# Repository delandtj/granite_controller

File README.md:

# granite

The Granite immersion frame electronics: the 48 V power plane, the
plane-core firmware, the controller and the software shared between them.

granite_controller and granite-plane merged on 2026-10-30. granite-plane
was split from granite_controller on 2026-10-29; its commits were replayed
on top of granite_controller's history, so both histories are here.

## Layout

- controller-fd: the controller with the CAN FD plane link (ADR 0006),
  the live design. tools/fd_build.sh builds it from the rev D board in
  attic/controller-rev-d.
- controller-rev-c: the rev C controller board (relays, expanders, 19 V
  input), kept as demoware. Tag rev-c-demo is the last rev C state of
  the whole repo, firmware included.
- power/pp-48-fd: plane tools and libraries for the CAN FD link
  (ADR 0006). power/pp-48-core-fd, power/pp-48-unit-fd: the chained plane
  (ADR 0005), one core board and identical 2-slot unit boards.
- power/pp-48: the I2C-link plane tools (schematic generator, placement
  and routing scripts), pp.kicad_sym, pp48.pretty, pp48.3dshapes; its
  schematic engine is also used by pm-19v-250w-b, and the attic boards
  use its libraries.
- power/pm-19v-250w, power/pm-19v-250w-b: the port module. power/pm-bench-carrier: bench
  carrier for one module. power/tools: module mount geometry.
- site: installer / operator manual (mdBook). Still describes rev C
  (relays, expanders, 19 V input); to be reworked for rev D and the plane.
- firmware: Rust workspace. granite-core (no_std: dispatcher, commands,
  MQTT / HTTP / Modbus surfaces, rules, config), granite-sim (host
  simulator), granite-fw (ESP32-C6 binary, still the rev C hardware
  layer), web UI.
- docs: ADRs 0001-0007, plane requirements, module interface, controller
  specs, handoff. Firmware ADRs in firmware/docs/adr.
- attic: superseded designs, kept for reference, not maintained.
  - attic/power/pp-48-2s: the first 2-slot plane (ADR 0001 / 0002).
  - attic/power/pm-19v-200w: the first port module (obsolete since
    2026-10-27, replaced by pm-19v-250w).
  - attic/power/pp-48-rev1: the single-board plane (ADR 0004, tag
    pp48-rev1); uses the libraries in power/pp-48.
  - attic/controller-rev-d: the I2C-link controller (rev D), superseded
    by controller-fd (2026-11-10); still the input board of
    controller-fd/tools/fd_build.sh.
  - attic/power/pp-48-core, attic/power/pp-48-unit: the I2C-link chained
    plane (ADR 0005), superseded by the -fd boards (2026-11-10); still the
    input boards of power/pp-48-fd/tools/fd_layout.sh and the output of
    power/pp-48/tools/gensch.py.
  - attic/firmware/plane-fw, attic/firmware/plane-core-pins.toml: the
    rev D plane binary (I2C link) and its pin map, frozen 2026-11-10;
    builds against firmware/granite-proto and firmware/plane-logic. The
    FD plane binary is firmware/plane-fd (firmware ADR 0005 decision 9).
  Older docs and the handoff name these at their old paths
  (power/pp-48-2s, power/pm-19v-200w, power/pp-48/pp-48.kicad_*,
  controller, power/pp-48-core, power/pp-48-unit).

## Direction (decided 2026-10-29)

- Plane core firmware on the STM32G070 (embassy), I2C slave to the
  controller, master to the units through the TCA9548A.
- Plane firmware updated from the controller over the link: own A/B
  bootloader (embassy-boot) that keeps the plane's strapped address,
  rollback on a failed self-test. ST's ROM bootloader only as a bench
  recovery path.
- The plane core owns node sequencing (press deadlines, power-cycle,
  retry / latch policy, stagger); the controller does policy, rules and
  the network.
- One controller serves several planes over isolated I2C (ISO1640 +
  EXP_INT, daisy chain, plane addresses 0x30-0x37).
- One TLV protocol crate used by the plane firmware, the controller and
  the simulator.
- Controller rev D: rev C minus the relays, expanders, LED sense and
  19 V input; 12 V from the plane's isolated aux.

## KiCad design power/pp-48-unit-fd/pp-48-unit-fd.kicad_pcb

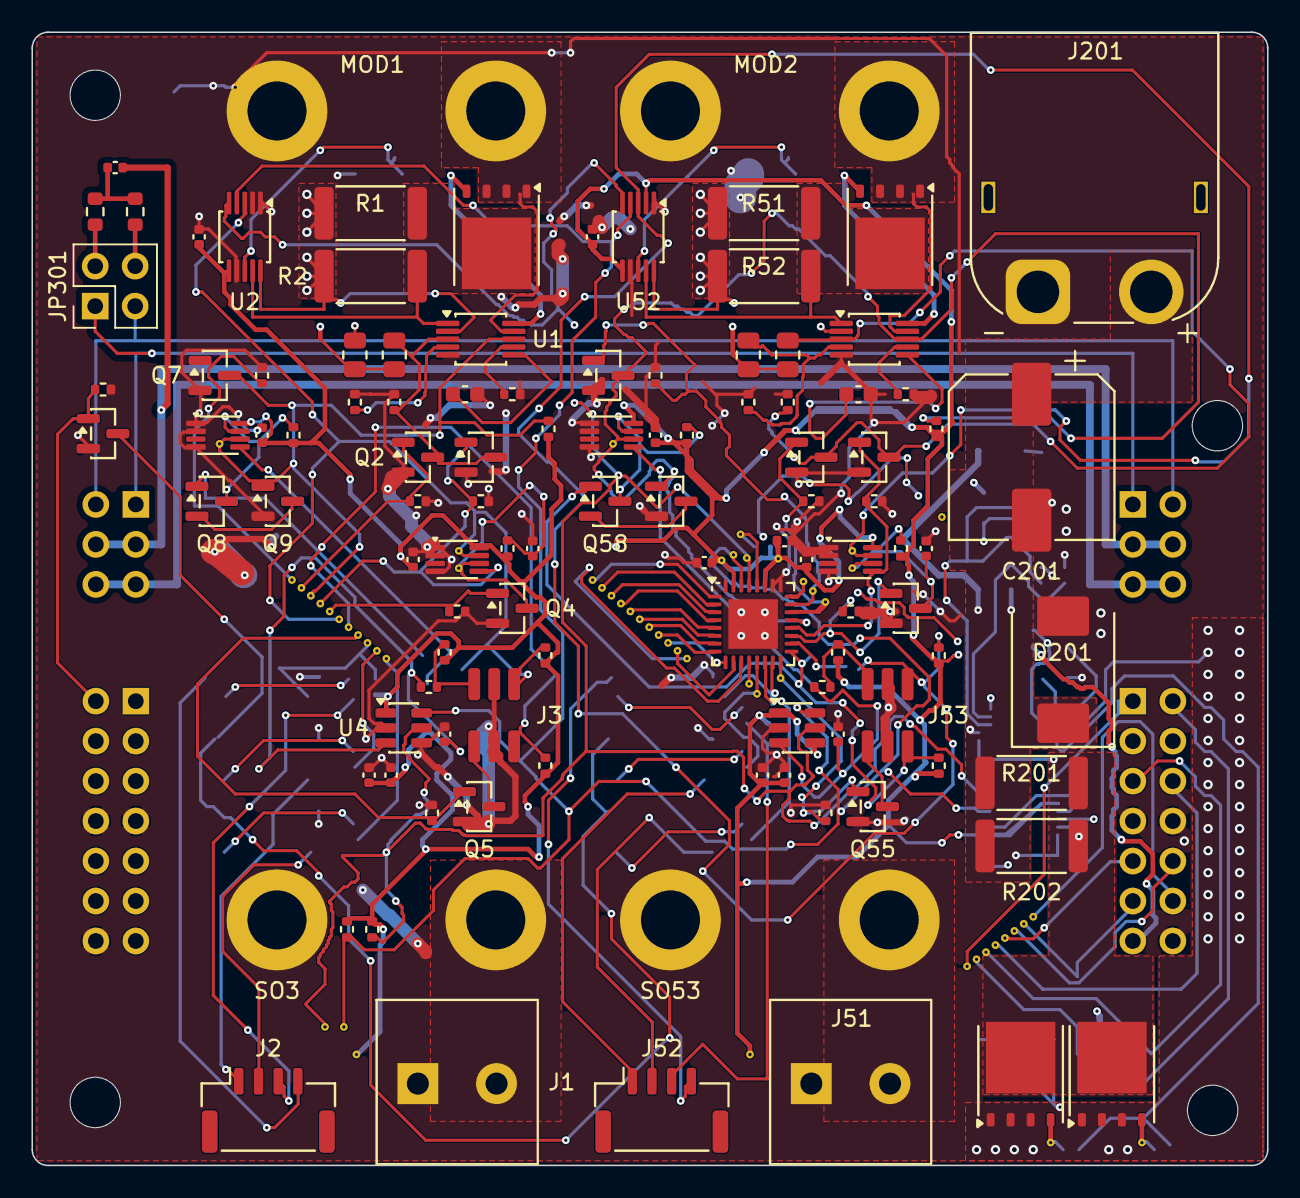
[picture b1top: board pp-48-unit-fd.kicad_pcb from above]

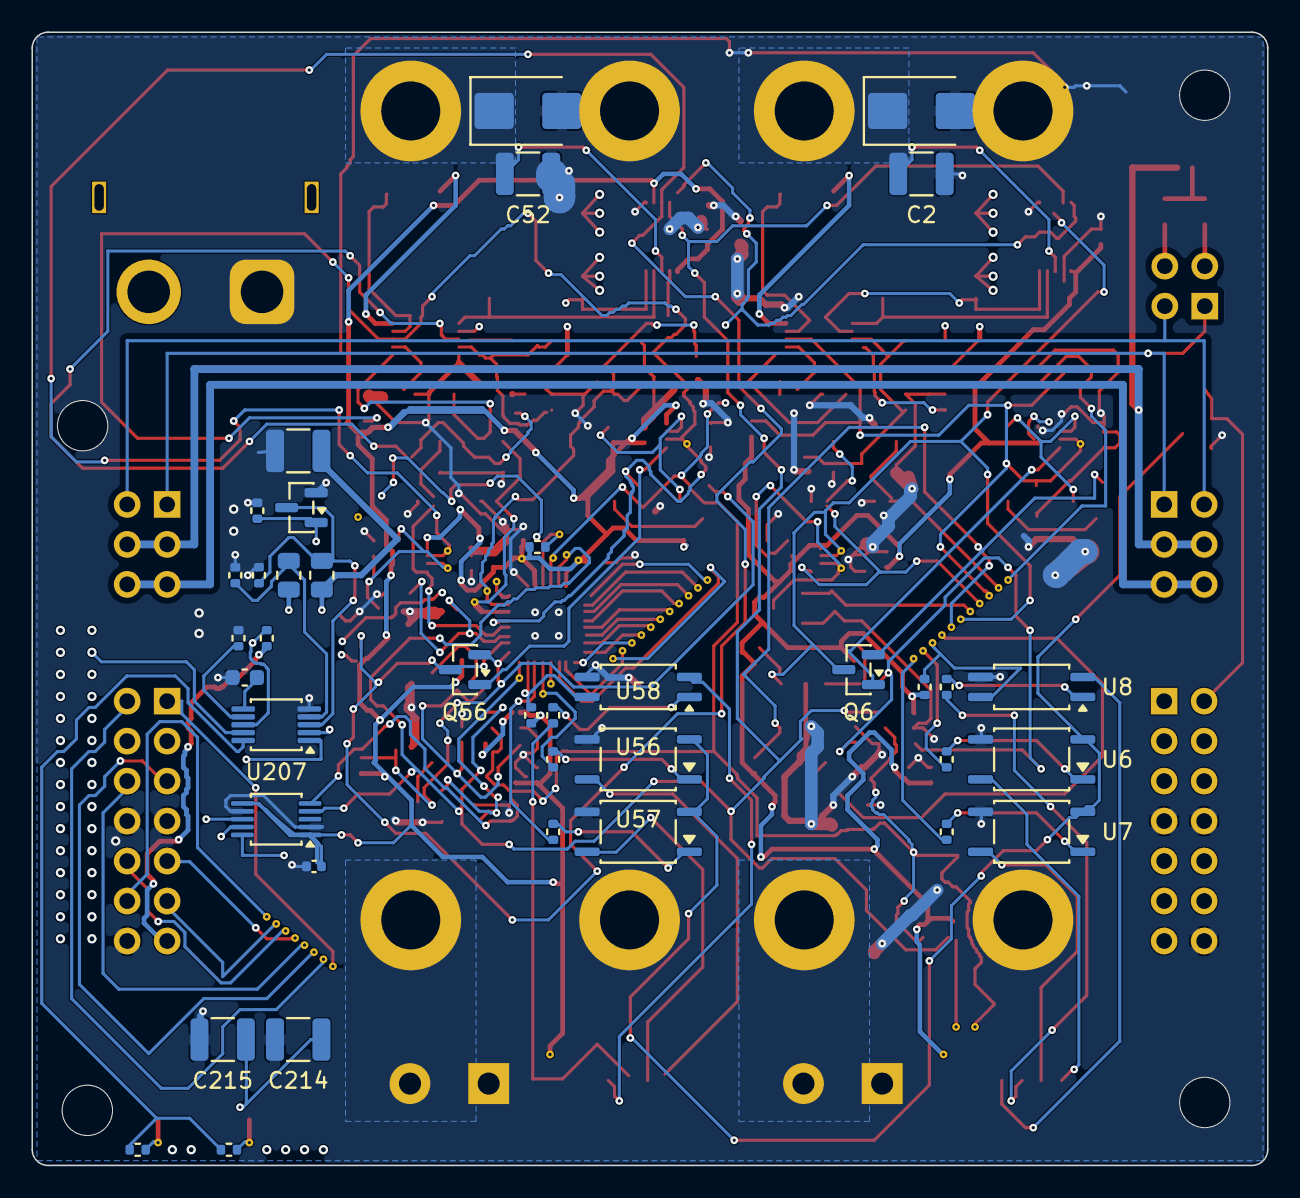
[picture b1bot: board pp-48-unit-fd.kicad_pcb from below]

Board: 4 copper layers, 78.5 x 72.0 mm, 214 parts (42 on the bottom side), 98 nets.

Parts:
BV100, BV101, BV102, BV103, BV104, BV105, BV106, BV107, BV108, BV109, BV110, BV150, BV151, BV152, BV153, BV154, BV155, BV156, BV157, BV158, BV159, BV160, BV900, BV901, BV902, BV903, BV904, BV905, BV906, BV907: (no value)
C1, C51, C203: 220n; C_0603_1608Metric
C2, C52, C202, C214, C215: 2.2u 100V; C_1210_3225Metric
C3, C4, C5, C6, C9, C10, C12, C13, C53, C54, C55, C56, C60, C62, C216: 100n; C_0402_1005Metric
C11, C61: 1u; C_0402_1005Metric
C201: 47u 100V; CP_Elec_10x10
C301: 4.7n; C_0402_1005Metric
D1, D51: SMBJ60A; D_SMB
D201: SMDJ60A; D_SMC
EV12, EV13, EV16, EV22, EV23, EV24, EV29, EV30: (no value)
GV202, GV203: (no value)
H1, H2, H3, H4: MountingHole_3.2mm_M3
J1, J51: NODE 19V; TerminalBlock_Degson_DG128-5.0-02P
J2, J52: FRONT PANEL; JST_GH_SM04B-GHS-TB_1x04-1MP_P1.25mm_Horizontal
J3, J53: AUX; PM_Aux_Socket_2x03_P1.27
J201: XT60PW-M; AMASS_XT60PW-M_1x02_P7.20mm_Horizontal
J301: CHAIN IN; PinHeader_2x07_P2.54mm_Horizontal
J302: CHAIN OUT; PinSocket_2x07_P2.54mm_Horizontal
J303: LINK IN; PinHeader_2x03_P2.54mm_Horizontal
J304: LINK OUT; PinSocket_2x03_P2.54mm_Horizontal
JP301: TERM; PinHeader_2x02_P2.54mm_Vertical
MOD1, MOD2: PM_Module_Outline
PV1B3, PV1B4, PV3A, PV3B: (no value)
Q1, Q51, Q202, Q203: ISC035N10NM5LF2; TDSON-8-1
Q2, Q3, Q4, Q5, Q6, Q7, Q8, Q9, Q10, Q52, Q53, Q54, Q55, Q56, Q57, Q58, Q59, Q204: 2N7002; SOT-23
R1, R2, R51, R52: 7m 2W; R_2512_6332Metric
R3, R53, R233: 143k; R_0805_2012Metric
R4, R8, R13, R14, R15, R30, R54, R58, R63, R64, R65, R234, R238: 10k; R_0402_1005Metric
R5, R55, R235: 124k; R_0805_2012Metric
R6, R56, R236: 4.99k; R_0402_1005Metric
R7, R57: 13.7k; R_0402_1005Metric
R9, R10, R11, R12, R23, R28, R29, R31, R59, R60, R61, R62, R73, R78, R79, R214: 100k; R_0402_1005Metric
R19, R20, R69, R70: 270; R_0402_1005Metric
R21, R71: 220; R_0402_1005Metric
R22, R72: 47k; R_0402_1005Metric
R24, R74: 1k; R_0402_1005Metric
R26, R27: 4.7k; R_0402_1005Metric
R201, R202: 6m 2W; R_2512_6332Metric
R210, R211: 10; R_0402_1005Metric
R237: 20.0k; R_0402_1005Metric
R301, R302: 60.4; R_0603_1608Metric
RV1: (no value)
SO1, SO51: S1 VIN; PM_Standoff_M2x7_SMTSO
SO2, SO52: S2 GND; PM_Standoff_M2x7_SMTSO
SO3, SO53: S3 GND; PM_Standoff_M2x7_SMTSO
SO4, SO54: S4 VOUT; PM_Standoff_M2x7_SMTSO
SV8, SV9: (no value)
U1, U51, U207: LM5069MM-2; MSOP-10_3x3mm_P0.5mm
U2, U52, U208: INA237AIDGSR; TSSOP-10_3x3mm_P0.5mm
U3, U10, U53, U60: 74LVC1G74; VSSOP-8_2.3x2mm_P0.5mm
U4, U54: ADC121C027CIMK; TSOT-23-6
U5: TCA6424ARGJR; VQFN-32-1EP_5x5mm_P0.5mm_EP3.15x3.15mm
U6, U7, U56, U57: TLP176AM; SOIC-4_4.55x3.7mm_P2.54mm
U8, U58: TLP291; SOIC-4_4.55x2.6mm_P1.27mm
UV1: (no value)
XV1A1, XV1A2, XV1A3, XV1B1, XV1B2, XV1B3: (no value)

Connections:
+3V3: C3.1, C4.1, C9.1, C10.1, C11.1, C12.1, C13.1, C53.1, C54.1, C60.1, C61.1, C62.1, C216.1, J301.13, J302.13, PV1B3.1, PV1B4.1, PV3A.1, PV3B.1, R8.1, R11.1, R13.1, R14.1, R15.1, R22.1, R26.1, R27.1, R28.1, R30.2, R58.1, R61.1, R63.1, R64.1, R65.1, R72.1, R78.1, R238.1, U2.6, U3.8, U4.1, U5.27, U5.31, U10.8, U52.2, U52.6, U53.8, U54.1, U54.4, U60.8, U208.1, U208.6
/Chain/AUX_12V: J303.5, J303.6, J304.5, J304.6
/Chain/CAN_N: J303.2, J304.2, JP301.3
/Chain/CAN_P: J303.1, J304.1, JP301.1
/Chain/CH1_SCL: BV907.1, J301.10, J302.12
/Chain/CH1_SDA: BV906.1, J301.9, J302.11
/Chain/CH2_SCL: BV905.1, J301.6, J302.10
/Chain/CH2_SDA: BV904.1, J301.5, J302.9
/Chain/CH3_SCL: BV903.1, J301.4, J302.6
/Chain/CH3_SDA: BV902.1, J301.3, J302.5
/Chain/LINK_GND: C301.2, J303.3, J303.4, J304.3, J304.4
/Chain/TERM_H: JP301.2, R301.1
/Chain/TERM_L: JP301.4, R302.2
/Chain/TERM_MID: C301.1, R301.2, R302.1
/EXP_RSTN: BV900.1, J301.1, J302.1, R30.1, RV1.1, U5.28
/Input/GATE: R210.1, R211.2, U207.10
/Input/OVLO: R235.2, R236.1, U207.4
/Input/PWR: R237.1, U207.7
/Input/TIMER: C203.1, U207.6
/Input/USENSE: Q202.5, Q203.5, R201.2, R202.2, U207.1, U208.9
/Input/UVLO: Q204.3, R233.2, R234.1, U207.3
/PRESS_EN: BV901.1, J301.2, J302.2, Q10.1, R31.1
/SEG_SCL: EV29.1, J301.12, R27.2, SV9.1, U2.5, U4.5, U5.29, U52.5, U54.5, U208.5
/SEG_SDA: EV30.1, J301.11, R26.2, SV8.1, U2.4, U4.6, U5.30, U52.4, U54.6, U208.4
/U_OFF: EV12.1, Q204.1, R214.1, U5.12, UV1.1
/U_PGD: EV24.1, R238.2, U5.24, U207.8
/Unit/A_ARM: Q6.1, U10.5
/Unit/A_ARMS_M: Q8.2, Q9.3
/Unit/A_ARMS_N: Q8.3, R28.2, U10.7
/Unit/A_CLRN: C5.1, Q4.3, R11.2, U3.6, XV1A2.1
/Unit/A_DISARM: BV100.1, BV150.1, Q7.1, R29.1, U5.1
/Unit/A_GATE: Q1.4, U1.10
/Unit/A_ID: J3.3, R15.2, R24.2
/Unit/A_ID_F: C6.1, R24.1, U4.3
/Unit/A_LCLR: BV104.1, BV154.1, Q4.1, R12.1, U5.5
/Unit/A_LED: BV108.1, BV158.1, R22.2, U5.9, U8.4
/Unit/A_LQ: BV103.1, BV153.1, Q3.1, R10.1, U3.5, U5.4
/Unit/A_NODE: J1.2, SO4.1
/Unit/A_OFF: BV101.1, BV151.1, Q2.1, R9.1, U5.2
/Unit/A_OUT: C2.1, D1.1, Q1.1, Q1.2, Q1.3, SO1.1, U1.9, U2.8
/Unit/A_OVK: BV105.1, BV155.1, J3.1, Q6.3, R13.2, U2.3, U3.7, U5.6, XV1A1.1
/Unit/A_OVLO: R5.2, R6.1, U1.4
/Unit/A_PG: BV106.1, BV156.1, J3.2, Q6.2, Q8.1, R14.2, U5.7
/Unit/A_PGD: BV102.1, BV152.1, Q7.3, Q9.1, R8.2, U1.8, U5.3, U10.6, XV1A3.1
/Unit/A_PLED_A: R21.2, U8.1
/Unit/A_PLED_N: J2.4, U8.2
/Unit/A_PLED_P: J2.3, R21.1
/Unit/A_PWR: R7.1, U1.7
/Unit/A_PWRD: BV109.1, BV159.1, R19.1, U5.10
/Unit/A_PWRD_A: R19.2, U6.1
/Unit/A_PWR_SW: J2.1, U6.6
/Unit/A_RSTD: BV110.1, BV160.1, R20.1, U5.11
/Unit/A_RSTD_A: R20.2, U7.1
/Unit/A_RST_SW: J2.2, U7.6
/Unit/A_RUN: J3.4, Q5.3
/Unit/A_RUNOFF: BV107.1, BV157.1, Q5.1, R23.1, U5.8
/Unit/A_SENSE: Q1.5, R1.2, R2.2, U1.1, U2.9
/Unit/A_TIMER: C1.1, U1.6
/Unit/A_UVLO: Q2.3, Q3.3, R3.2, R4.1, U1.3
/Unit/B_ARM: Q56.1, U60.5
/Unit/B_ARMS_M: Q58.2, Q59.3
/Unit/B_ARMS_N: Q58.3, R78.2, U60.7
/Unit/B_CLRN: C55.1, Q54.3, R61.2, U53.6, XV1B2.1
/Unit/B_DISARM: EV23.1, Q57.1, R79.1, U5.23
/Unit/B_GATE: Q51.4, U51.10
/Unit/B_ID: J53.3, R65.2, R74.2
/Unit/B_ID_F: C56.1, R74.1, U54.3
/Unit/B_LCLR: Q54.1, R62.1, U5.19
/Unit/B_LED: R72.2, U5.15, U58.4
/Unit/B_LQ: Q53.1, R60.1, U5.20, U53.5
/Unit/B_NODE: J51.2, SO54.1
/Unit/B_OFF: EV22.1, Q52.1, R59.1, U5.22
/Unit/B_OUT: C52.1, D51.1, Q51.1, Q51.2, Q51.3, SO51.1, U51.9, U52.8
/Unit/B_OVK: J53.1, Q56.3, R63.2, U5.18, U52.3, U53.7, XV1B1.1
/Unit/B_OVLO: R55.2, R56.1, U51.4
/Unit/B_PG: J53.2, Q56.2, Q58.1, R64.2, U5.17
/Unit/B_PGD: Q57.3, Q59.1, R58.2, U5.21, U51.8, U60.6, XV1B3.1
/Unit/B_PLED_A: R71.2, U58.1
/Unit/B_PLED_N: J52.4, U58.2
/Unit/B_PLED_P: J52.3, R71.1
/Unit/B_PWR: R57.1, U51.7
/Unit/B_PWRD: EV13.1, R69.1, U5.13
/Unit/B_PWRD_A: R69.2, U56.1
/Unit/B_PWR_SW: J52.1, U56.6
/Unit/B_RSTD: R70.1, U5.14
/Unit/B_RSTD_A: R70.2, U57.1
/Unit/B_RST_SW: J52.2, U57.6
/Unit/B_RUN: J53.4, Q55.3
/Unit/B_RUNOFF: EV16.1, Q55.1, R73.1, U5.16
/Unit/B_SENSE: Q51.5, R51.2, R52.2, U51.1, U52.9
/Unit/B_TIMER: C51.1, U51.6
/Unit/B_UVLO: Q52.3, Q53.3, R53.2, R54.1, U51.3
/Unit/PRESS_RTN: Q10.3, U6.3, U7.3, U56.3, U57.3
GND: C1.2, C2.2, C3.2, C4.2, C5.2, C6.2, C9.2, C10.2, C11.2, C12.2, C13.2, C51.2, C52.2, C53.2, C54.2, C55.2, C56.2, C60.2, C61.2, C62.2, C201.2, C202.2, C203.2, C214.2, C215.2, C216.2, D1.2, D51.2, D201.2, J1.1, J3.5, J3.6, J51.1, J53.5, J53.6, J201.1, J301.7, J301.8, J301.14, J302.7, J302.8, J302.14, Q2.2, Q3.2, Q4.2, Q5.2, Q7.2, Q9.2, Q10.2, Q52.2, Q53.2, Q54.2, Q55.2, Q57.2, Q59.2, Q204.2, R4.2, R6.2, R7.2, R9.2, R10.2, R12.2, R23.2, R29.2, R31.2, R54.2, R56.2, R57.2, R59.2, R60.2, R62.2, R73.2, R79.2, R214.2, R234.2, R236.2, R237.2, SO2.1, SO3.1, SO52.1, SO53.1, U1.5, U2.1, U2.2, U2.7, U3.1, U3.2, U3.4, U4.2, U4.4, U5.25, U5.26, U5.33, U6.4, U7.4, U8.3, U10.1, U10.2, U10.4, U51.5, U52.1, U52.7, U53.1, U53.2, U53.4, U54.2, U56.4, U57.4, U58.3, U60.1, U60.2, U60.4, U207.5, U208.2, U208.7
unnamed: GV202.1, Q202.4, R210.2
unnamed: GV203.1, Q203.4, R211.1
VBUS: C214.1, C215.1, Q202.1, Q202.2, Q202.3, Q203.1, Q203.2, Q203.3, R1.1, R2.1, R3.1, R5.1, R51.1, R52.1, R53.1, R55.1, U1.2, U2.10, U51.2, U52.10, U207.9, U208.8
VIN: C201.1, C202.1, D201.1, J201.2, R201.1, R202.1, R233.1, R235.1, U207.2, U208.10

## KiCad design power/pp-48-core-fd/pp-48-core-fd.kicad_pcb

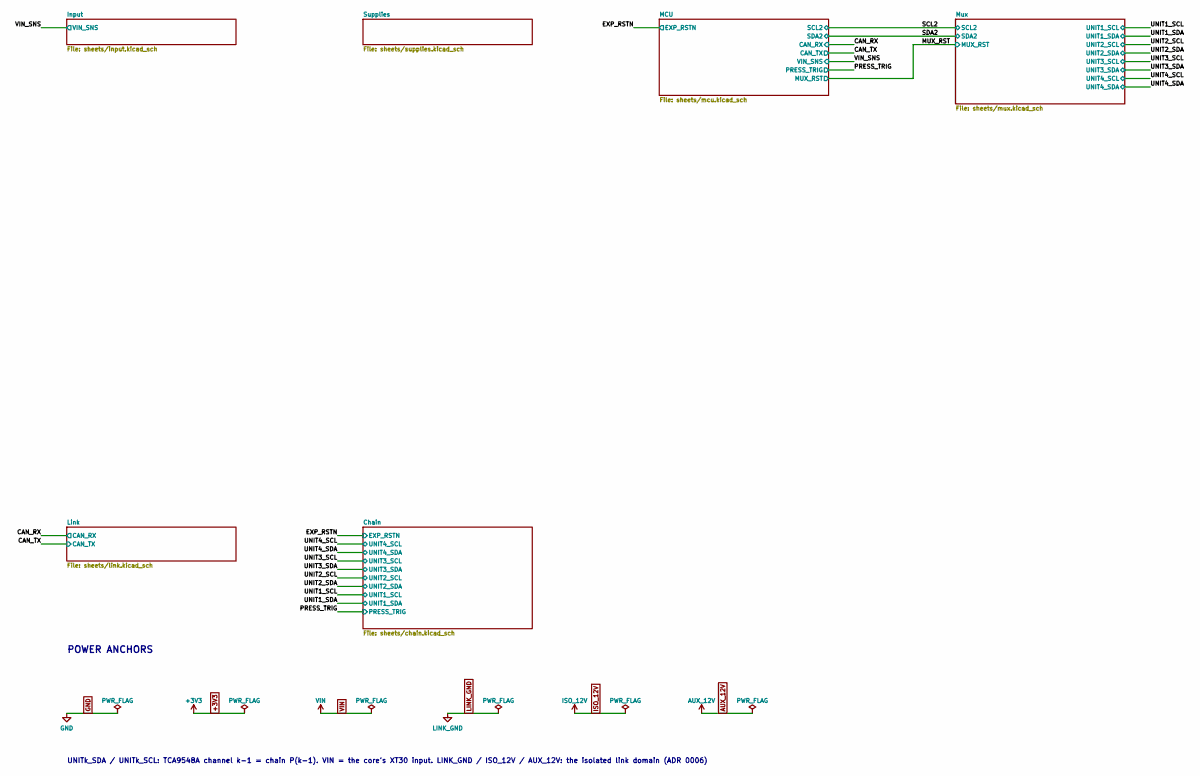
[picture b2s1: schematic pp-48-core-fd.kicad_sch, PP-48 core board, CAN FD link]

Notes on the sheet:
POWER ANCHORS
UNITk_SDA / UNITk_SCL: TCA9548A channel k-1 = chain P(k-1). VIN = the core's XT30 input. LINK_GND / ISO_12V / AUX_12V: the isolated link domain (ADR 0006)

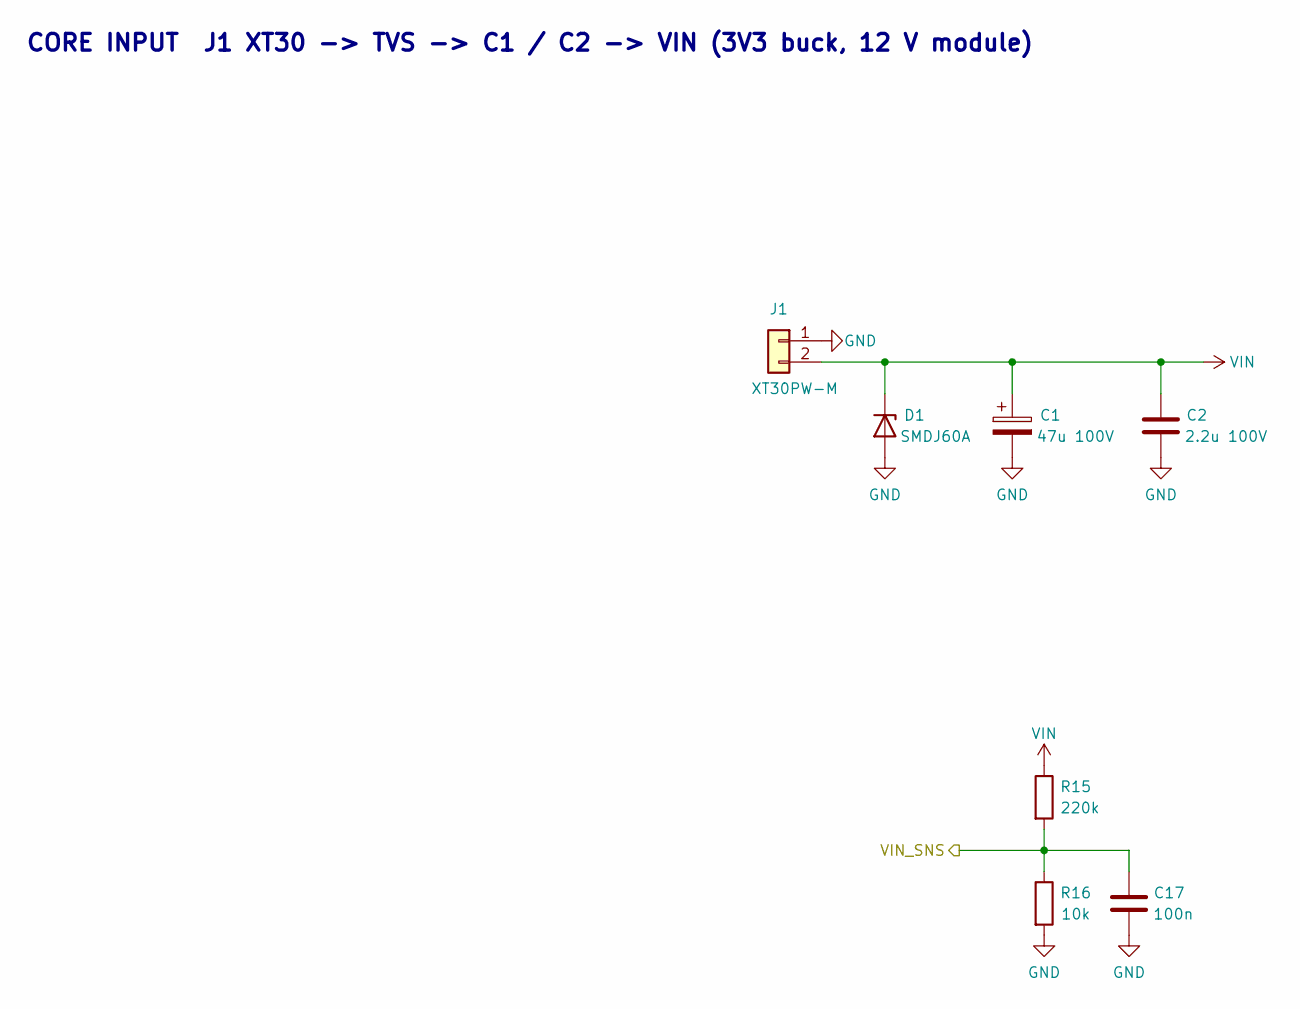
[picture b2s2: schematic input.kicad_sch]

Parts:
C1: 47u 100V; CP_Elec_10x10; MPN Lelon RVT2A470M1010; LCSC C87862
C2: 2.2u 100V; C_1210_3225Metric; LCSC C338133
C17: 100n; C_0402_1005Metric; LCSC C1525
D1: SMDJ60A; D_SMC; LCSC C2990209
J1: XT30PW-M; AMASS_XT30PW-M_1x02_P2.50mm_Horizontal; MPN Amass XT30PW-M; LCSC C431092
R15: 220k; R_0805_2012Metric; LCSC C17556
R16: 10k; R_0402_1005Metric; LCSC C25744

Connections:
/VIN_SNS: C17.1, R15.2, R16.1; also elsewhere on the board
GND: C1.2, C2.2, C17.2, D1.2 (A), J1.1, R16.2; also elsewhere on the board
VIN: C1.1, C2.1, D1.1 (K), J1.2, R15.1; also elsewhere on the board

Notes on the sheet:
CORE INPUT J1 XT30 -> TVS -> C1 / C2 -> VIN (3V3 buck, 12 V module)

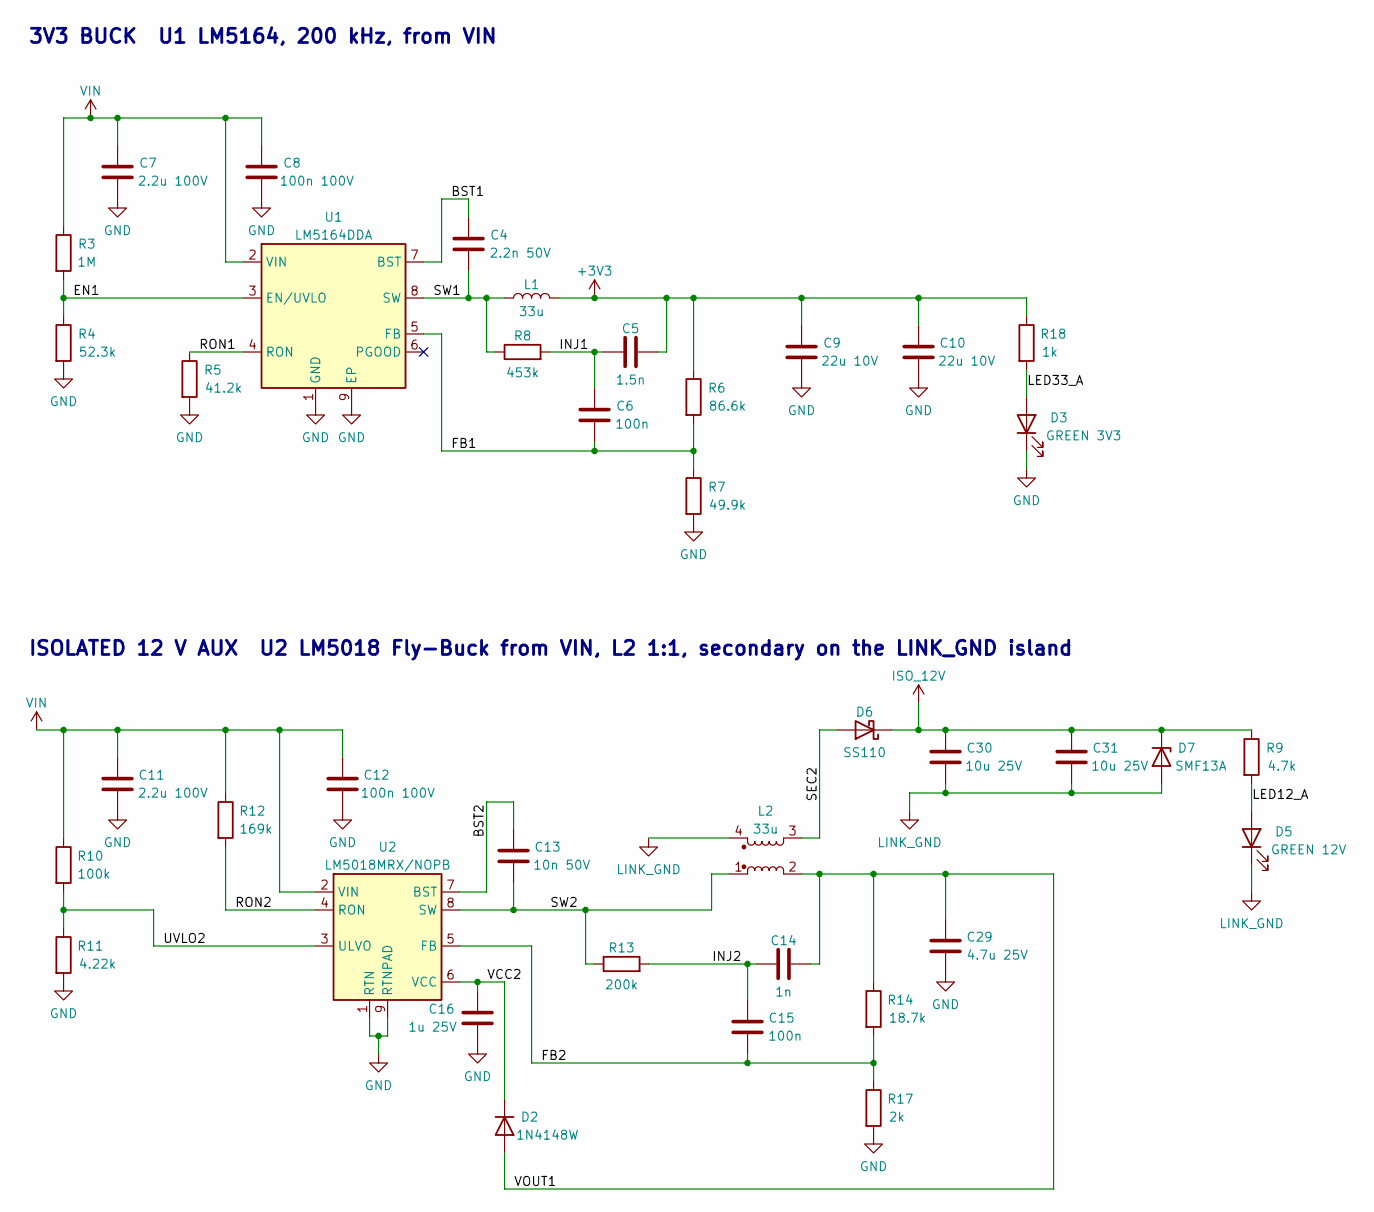
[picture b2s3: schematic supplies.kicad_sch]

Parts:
C4: 2.2n 50V; C_0402_1005Metric; LCSC C1531
C5: 1.5n; C_0402_1005Metric; LCSC C107022
C6, C15: 100n; C_0402_1005Metric; LCSC C1525
C7, C11: 2.2u 100V; C_1210_3225Metric; LCSC C338133
C8, C12: 100n 100V; C_0603_1608Metric; LCSC C696916
C9, C10: 22u 10V; C_1210_3225Metric; LCSC C318780
C13: 10n 50V; C_0402_1005Metric; LCSC C15195
C14: 1n; C_0402_1005Metric; LCSC C1523
C16: 1u 25V; C_0603_1608Metric; LCSC C15849
C29: 4.7u 25V; C_0805_2012Metric; LCSC C1779
C30, C31: 10u 25V; C_0805_2012Metric; LCSC C15850
D2: 1N4148W; D_SOD-123; LCSC C917030
D3: GREEN 3V3; LED_0603_1608Metric; LCSC C12624
D5: GREEN 12V; LED_0603_1608Metric; LCSC C12624
D6: SS110; D_SMA; LCSC C2482
D7: SMF13A; D_SOD-123F; LCSC C353315
L1: 33u; L_Bourns_SRR1260; MPN Bourns SRR1260-330M; LCSC C840528
L2: 33u; L_Coilcraft_LPD5030V; MPN Coilcraft LPD5030V-333MRC; LCSC C5441621
R3: 1M; R_0805_2012Metric; LCSC C17514
R4: 52.3k; R_0402_1005Metric; LCSC C2998086
R5: 41.2k; R_0402_1005Metric; LCSC C2998053
R6: 86.6k; R_0402_1005Metric; LCSC C48533697
R7: 49.9k; R_0402_1005Metric; LCSC C137969
R8: 453k; R_0402_1005Metric; LCSC C27009
R9: 4.7k; R_0603_1608Metric; LCSC C23162
R10: 100k; R_0805_2012Metric; LCSC C149504
R11: 4.22k; R_0402_1005Metric; LCSC C25898
R12: 169k; R_0805_2012Metric; LCSC C2933337
R13: 200k; R_0805_2012Metric; LCSC C17539
R14: 18.7k; R_0402_1005Metric; LCSC C5153953
R17: 2k; R_0402_1005Metric; LCSC C4109
R18: 1k; R_0402_1005Metric; LCSC C11702
U1: LM5164DDA; HSOP-8-1EP_3.9x4.9mm_P1.27mm_EP2.41x3.1mm; LCSC C477928
U2: LM5018MRX/NOPB; SOIC-8-1EP_3.9x4.9mm_P1.27mm_EP2.95x4.9mm_Mask2.71x3.4mm_Th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; LCSC C471040

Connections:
+3V3: C5.2, C9.1, C10.1, L1.2, R6.1, R18.1; also elsewhere on the board
/Supplies/BST1: C4.1, U1.7 (BST)
/Supplies/BST2: C13.1, U2.7 (BST)
/Supplies/EN1: R3.2, R4.1, U1.3 (EN/UVLO)
/Supplies/FB1: C6.2, R6.2, R7.1, U1.5 (FB)
/Supplies/FB2: C15.2, R14.2, R17.1, U2.5 (FB)
/Supplies/INJ1: C5.1, C6.1, R8.2
/Supplies/INJ2: C14.1, C15.1, R13.2
/Supplies/LED12_A: D5.2 (A), R9.2
/Supplies/LED33_A: D3.2 (A), R18.2
/Supplies/RON1: R5.1, U1.4 (RON)
/Supplies/RON2: R12.2, U2.4 (RON)
/Supplies/SEC2: D6.2 (A), L2.3
/Supplies/SW1: C4.2, L1.1, R8.1, U1.8 (SW)
/Supplies/SW2: C13.2, L2.1, R13.1, U2.8 (SW)
/Supplies/UVLO2: R10.2, R11.1, U2.3 (ULVO)
/Supplies/VCC2: C16.1, D2.1 (K), U2.6 (VCC)
/Supplies/VOUT1: C14.2, C29.1, D2.2 (A), L2.2, R14.1
GND: C7.2, C8.2, C9.2, C10.2, C11.2, C12.2, C16.2, C29.2, D3.1 (K), R4.2, R5.2, R7.2, R11.2, R17.2, U1.1 (GND), U1.9 (EP), U2.1 (RTN), U2.9 (RTNPAD); also elsewhere on the board
ISO_12V: C30.1, C31.1, D6.1 (K), D7.1 (K), R9.1; also elsewhere on the board
LINK_GND: C30.2, C31.2, D5.1 (K), D7.2 (A), L2.4; also elsewhere on the board
VIN: C7.1, C8.1, C11.1, C12.1, R3.1, R10.1, R12.1, U1.2 (VIN), U2.2 (VIN); also elsewhere on the board

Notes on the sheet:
3V3 BUCK U1 LM5164, 200 kHz, from VIN
ISOLATED 12 V AUX U2 LM5018 Fly-Buck from VIN, L2 1:1, secondary on the LINK_GND island

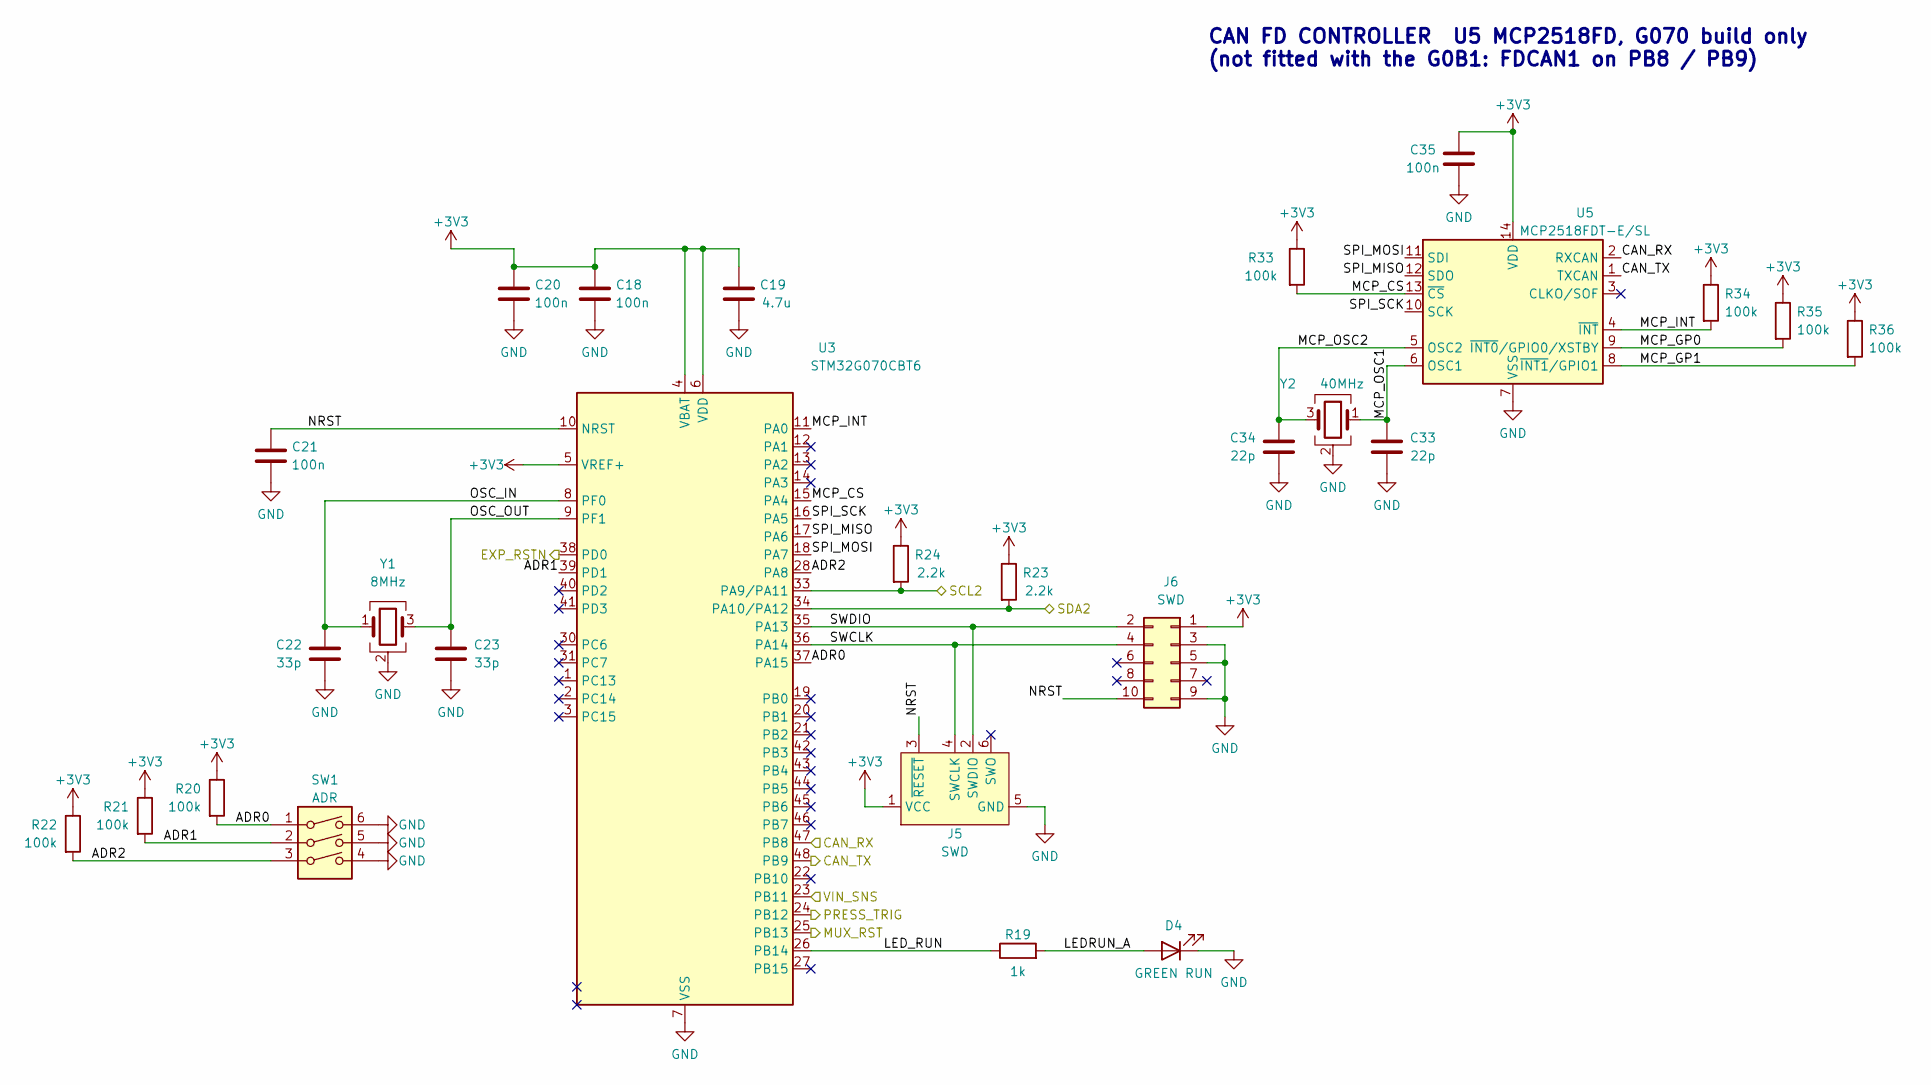
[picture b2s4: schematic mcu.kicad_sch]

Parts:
C18, C20, C21: 100n; C_0402_1005Metric; LCSC C1525
C19: 4.7u; C_0603_1608Metric; LCSC C19666
C22, C23: 33p; C_0402_1005Metric; LCSC C1562
C33, C34: 22p; C_0402_1005Metric; MPN FH 0402CG220J500NT; LCSC C1555
C35: 100n; C_0402_1005Metric; MPN Samsung CL05B104KO5NNNC; LCSC C1525
D4: GREEN RUN; LED_0603_1608Metric; LCSC C12624
J5: SWD; Tag-Connect_TC2030-IDC-NL_2x03_P1.27mm_Vertical
J6: SWD; PinHeader_2x05_P1.27mm_Vertical_SMD; MPN Samtec FTSH-105-01-L-DV-K; LCSC C5155080
R19: 1k; R_0402_1005Metric; LCSC C11702
R20, R21, R22: 100k; R_0402_1005Metric; LCSC C25741
R23, R24: 2.2k; R_0402_1005Metric; LCSC C25879
R33, R34, R35, R36: 100k; R_0402_1005Metric; MPN UniOhm 0402WGF1003TCE; LCSC C25741
SW1: ADR; SW_DIP_SPSTx03_Slide_KingTek_DSHP03TS_W7.62mm_P1.27mm; MPN KingTek DSHP03TSGET; LCSC C50844
U3: STM32G070CBT6; LQFP-48_7x7mm_P0.5mm; LCSC C529338
U5: MCP2518FDT-E/SL; SOIC-14_3.9x8.7mm_P1.27mm; MPN Microchip MCP2518FDT-E/SL; LCSC C626758
Y1: 8MHz; Crystal_SMD_3225-4Pin_3.2x2.5mm; LCSC C7424755
Y2: 40MHz; Crystal_SMD_3225-4Pin_3.2x2.5mm; MPN YXC X322540MPB4SI; LCSC C9010

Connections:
+3V3: C18.1, C19.1, C20.1, C35.1, J5.1 (VCC), J6.1, R20.1, R21.1, R22.1, R23.1, R24.1, R33.1, R34.1, R35.1, R36.1, U3.4 (VBAT), U3.5 (VREF+), U3.6 (VDD), U5.14 (VDD); also elsewhere on the board
/CAN_RX: U3.47 (PB8), U5.2 (RXCAN); also elsewhere on the board
/CAN_TX: U3.48 (PB9), U5.1 (TXCAN); also elsewhere on the board
/EXP_RSTN: U3.38 (PD0); also elsewhere on the board
/MCU/ADR0: R20.2, SW1.1, U3.37 (PA15)
/MCU/ADR1: R21.2, SW1.2, U3.39 (PD1)
/MCU/ADR2: R22.2, SW1.3, U3.28 (PA8)
/MCU/LEDRUN_A: D4.2 (A), R19.2
/MCU/LED_RUN: R19.1, U3.26 (PB14)
/MCU/MCP_CS: R33.2, U3.15 (PA4), U5.13 (~CS)
/MCU/MCP_GP0: R35.2, U5.9 (~INT0/GPIO0/XSTBY)
/MCU/MCP_GP1: R36.2, U5.8 (~INT1/GPIO1)
/MCU/MCP_INT: R34.2, U3.11 (PA0), U5.4 (~INT)
/MCU/MCP_OSC1: C33.1, U5.6 (OSC1), Y2.1
/MCU/MCP_OSC2: C34.1, U5.5 (OSC2), Y2.3
/MCU/NRST: C21.1, J5.3 (~RESET), J6.10, U3.10 (NRST)
/MCU/OSC_IN: C22.1, U3.8 (PF0), Y1.1
/MCU/OSC_OUT: C23.1, U3.9 (PF1), Y1.3
/MCU/SPI_MISO: U3.17 (PA6), U5.12 (SDO)
/MCU/SPI_MOSI: U3.18 (PA7), U5.11 (SDI)
/MCU/SPI_SCK: U3.16 (PA5), U5.10 (SCK)
/MCU/SWCLK: J5.4 (SWCLK), J6.4, U3.36 (PA14)
/MCU/SWDIO: J5.2 (SWDIO), J6.2, U3.35 (PA13)
/MUX_RST: U3.25 (PB13); also elsewhere on the board
/PRESS_TRIG: U3.24 (PB12); also elsewhere on the board
/SCL2: R24.2, U3.33 (PA9/PA11); also elsewhere on the board
/SDA2: R23.2, U3.34 (PA10/PA12); also elsewhere on the board
/VIN_SNS: U3.23 (PB11); also elsewhere on the board
GND: C18.2, C19.2, C20.2, C21.2, C22.2, C23.2, C33.2, C34.2, C35.2, D4.1 (K), J5.5 (GND), J6.3, J6.5, J6.9, SW1.4, SW1.5, SW1.6, U3.7 (VSS), U5.7 (VSS), Y1.2 (G), Y1.4 (G), Y2.2 (G), Y2.4 (G); also elsewhere on the board

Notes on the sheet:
CAN FD CONTROLLER U5 MCP2518FD, G070 build only (not fitted with the G0B1: FDCAN1 on PB8 / PB9)

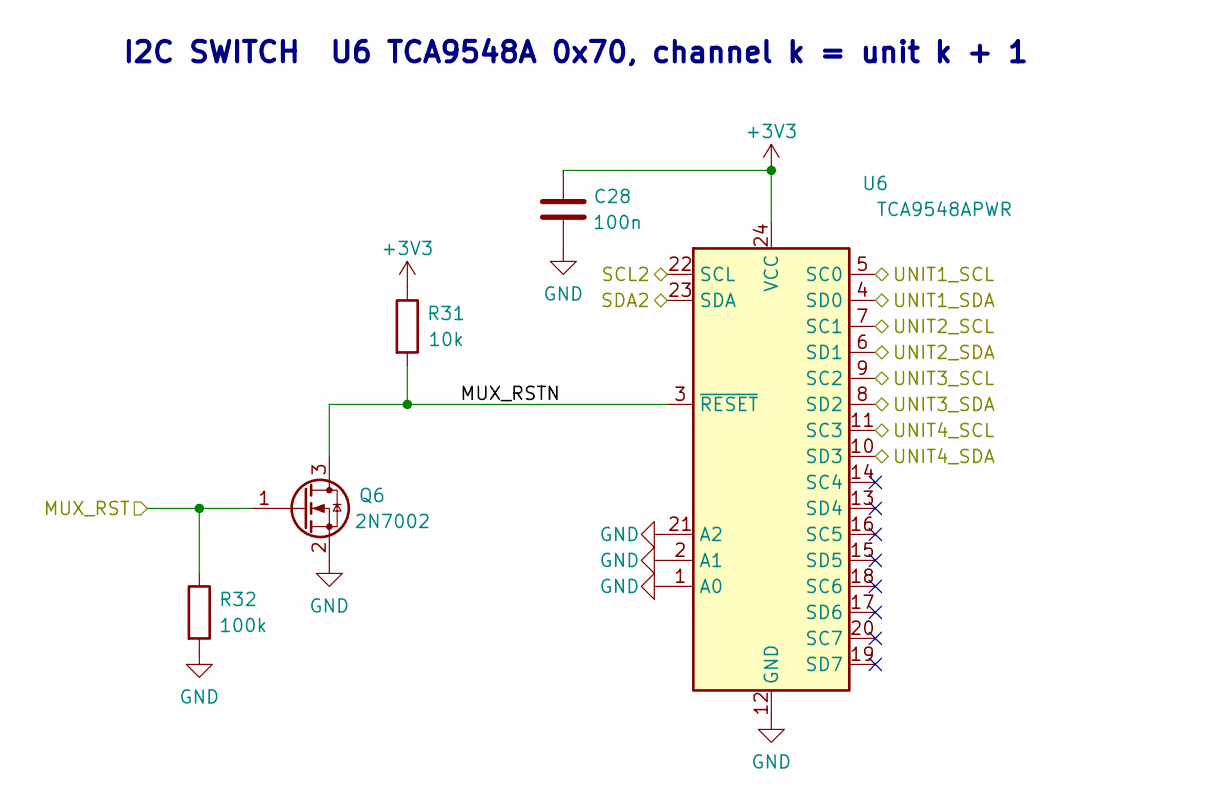
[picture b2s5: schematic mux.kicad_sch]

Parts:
C28: 100n; C_0402_1005Metric; LCSC C1525
Q6: 2N7002; SOT-23; LCSC C8545
R31: 10k; R_0402_1005Metric; LCSC C25744
R32: 100k; R_0402_1005Metric; LCSC C25741
U6: TCA9548APWR; TSSOP-24_4.4x7.8mm_P0.65mm; LCSC C130026

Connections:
+3V3: C28.1, R31.1, U6.24 (VCC); also elsewhere on the board
/MUX_RST: Q6.1 (G), R32.1; also elsewhere on the board
/Mux/MUX_RSTN: Q6.3 (D), R31.2, U6.3 (~RESET)
/SCL2: U6.22 (SCL); also elsewhere on the board
/SDA2: U6.23 (SDA); also elsewhere on the board
/UNIT1_SCL: U6.5 (SC0); also elsewhere on the board
/UNIT1_SDA: U6.4 (SD0); also elsewhere on the board
/UNIT2_SCL: U6.7 (SC1); also elsewhere on the board
/UNIT2_SDA: U6.6 (SD1); also elsewhere on the board
/UNIT3_SCL: U6.9 (SC2); also elsewhere on the board
/UNIT3_SDA: U6.8 (SD2); also elsewhere on the board
/UNIT4_SCL: U6.11 (SC3); also elsewhere on the board
/UNIT4_SDA: U6.10 (SD3); also elsewhere on the board
GND: C28.2, Q6.2 (S), R32.2, U6.1 (A0), U6.2 (A1), U6.12 (GND), U6.21 (A2); also elsewhere on the board

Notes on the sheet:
I2C SWITCH U6 TCA9548A 0x70, channel k = unit k + 1
